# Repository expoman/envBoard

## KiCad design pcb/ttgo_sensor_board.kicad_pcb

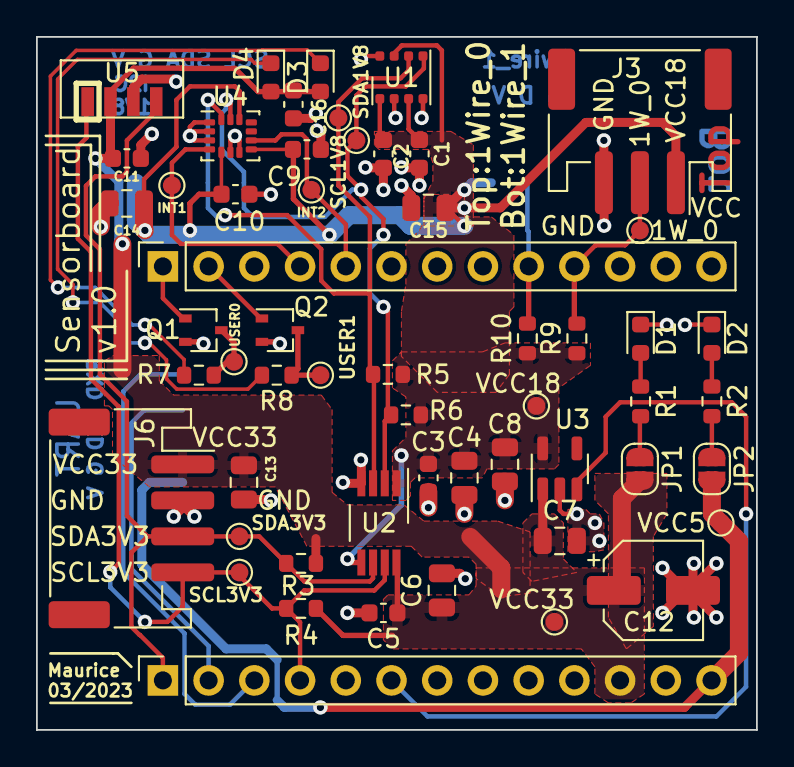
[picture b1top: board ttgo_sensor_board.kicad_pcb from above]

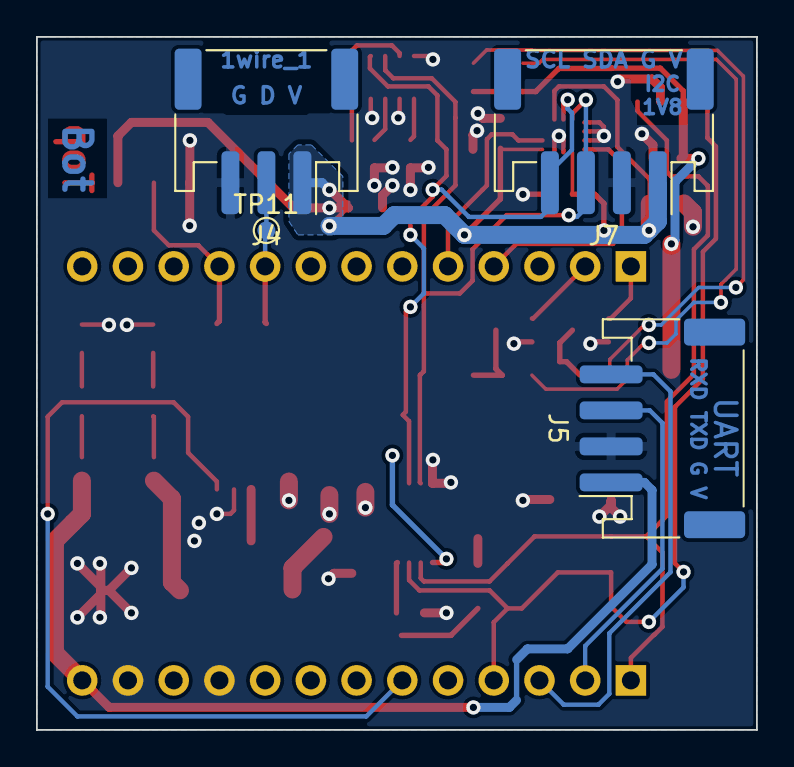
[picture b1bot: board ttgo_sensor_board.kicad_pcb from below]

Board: 2 copper layers, 40.0 x 38.5 mm, 59 parts (4 on the bottom side), 25 nets.

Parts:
C1, C2, C3, C5, C9, C10, C11, C16: 100nF; C_0603_1608Metric
C4, C6, C7, C8, C13, C14, C15: 1uF; C_0805_2012Metric
C12: 10uF; CP_Elec_5x5.3
D1: VCC33_Green; LED_0603_1608Metric
D2: VCC5_Green; LED_0603_1608Metric
D3: U0; LED_0603_1608Metric
D4: U1; LED_0603_1608Metric
J1, J2: Conn_01x13_Female; PinSocket_1x13_P2.54mm_Vertical
J3, J4: Conn_01x03_Female; JST_PH_S3B-PH-SM4-TB_1x03-1MP_P2.00mm_Horizontal
J5, J6, J7: Conn_01x04_Female; JST_PH_S4B-PH-SM4-TB_1x04-1MP_P2.00mm_Horizontal
JP1, JP2: SolderJumper_2_Open; SolderJumper-2_P1.3mm_Open_RoundedPad1.0x1.5mm
Q1, Q2: Q_NMOS_GSD; SOT-323_SC-70
R1: 120; R_0603_1608Metric
R2: 300; R_0603_1608Metric
R3, R4, R5, R6: 10k; R_0603_1608Metric
R7, R8: 82; R_0603_1608Metric
R9, R10: 4k7; R_0603_1608Metric
TP1: VCC33; TestPoint_Pad_D1.0mm
TP2: USER0; TestPoint_Pad_D1.0mm
TP3: USER1; TestPoint_Pad_D1.0mm
TP4: VCC18; TestPoint_Pad_D1.0mm
TP5: VCC5; TestPoint_Pad_D1.0mm
TP6: SCL3V3; TestPoint_Pad_D1.0mm
TP7: SDA3V3; TestPoint_Pad_D1.0mm
TP8: SCL1V8; TestPoint_Pad_D1.0mm
TP9: SDA1V8; TestPoint_Pad_D1.0mm
TP10: 1W_0; TestPoint_Pad_D1.0mm
TP11: 1W_1; TestPoint_Pad_D1.0mm
TP12: INT1; TestPoint_Pad_D1.0mm
TP13: INT2; TestPoint_Pad_D1.0mm
U1: BME680; Bosch_LGA-8_3x3mm_P0.8mm_ClockwisePinNumbering
U2: TCA9800; VSSOP-8_3.0x3.0mm_P0.65mm
U3: TLV70218_SOT23-5; SOT-23-5
U4: LSM6DS3; LGA-14_3x2.5mm_P0.5mm_LayoutBorder3x4y
U5: VEML7700; VEML7700_top_view

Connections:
/1WIRE_DATA0: J2.10, J3.2, R9.2, TP10.1
/1WIRE_DATA1: J2.9, J4.2, R10.2, TP11.1
/EN1V8: J1.6, U3.3 (EN)
/GPIO01: J1.2, J5.3
/GPIO03: J1.3, J5.4
/GPIO21: J1.1, J6.3, R3.2, TP7.1, U2.6 (SDAB), U5.4 (SDA)
/GPIO22: J1.4, J6.4, R4.2, TP6.1, U2.7 (SCLB), U5.1 (SCL)
/GPIO34: J2.4, TP12.1, U4.4 (INT1)
/GPIO35: J2.5, TP13.1, U4.9 (INT2)
/GPIO36: J2.1, Q1.1 (G)
/GPIO39: J2.2, Q2.1 (G)
/SCL1V8: J7.4, R6.2, TP8.1, U1.4 (SCK), U2.2 (SCLA), U4.13 (SCL)
/SDA1V8: J7.3, R5.2, TP9.1, U1.3 (SDI), U2.3 (SDAA), U4.14 (SDA)
/VCC5: J1.13, J5.1, JP2.2 (B), TP5.1
/VCC18: C1.1, C2.1, C3.1, C4.1, C8.1, C9.1, C10.1, C14.1, C15.1, J3.1, J4.1, J7.1, R5.1, R6.1, R9.1, R10.1, TP4.1, U1.2 (CSB), U1.6 (VDDIO), U1.8 (VDD), U2.1 (VCCA), U2.5 (EN), U3.5 (OUT), U4.5 (VDDIO), U4.8 (VDD), U4.12 (CS)
/VCC33: C5.1, C6.1, C7.1, C11.1, C12.1, C13.1, C16.1, D3.2 (A), D4.2 (A), J1.11, J6.1, JP1.2 (B), R3.1, R4.1, TP1.1, U2.8 (VCCB), U3.1 (IN), U5.2 (VDD)
GND: C1.2, C2.2, C3.2, C4.2, C5.2, C6.2, C7.2, C8.2, C9.2, C10.2, C11.2, C12.2, C13.2, C14.2, C15.2, C16.2, D1.1 (K), D2.1 (K), J1.10, J1.12, J3.3, J4.3, J5.2, J6.2, J7.2, Q1.2 (S), Q2.2 (S), U1.1 (GND), U1.5 (SDO), U1.7 (GND), U2.4 (GND), U3.2 (GND), U4.1 (SDO/SA0), U4.2 (SDX), U4.3 (SCX), U4.6 (GND), U4.7 (GND), U5.3 (GND)
unnamed: D1.2 (A), R1.1
unnamed: D2.2 (A), R2.1
unnamed: D3.1 (K), R7.2
unnamed: D4.1 (K), R8.2
unnamed: JP1.1 (A), R1.2
unnamed: JP2.1 (A), R2.2
unnamed: Q1.3 (D), R7.1, TP2.1
unnamed: Q2.3 (D), R8.1, TP3.1

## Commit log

2023-03-24 add gitignore file
2023-03-24 initial commit with kicad files
2023-03-30 remove backupt files
2023-03-30 backup current state
2023-03-30 moved leds and change silkscreen
2023-04-15 production state
2023-06-08 fix schematic after first prototype
2023-06-08 restructure repo: add pcb folder
2023-06-08 add testing versions of firmware
2023-06-29 add basic example for ttgo lora32 v2
2023-06-29 advance ttgo_sensor
    read vcc/vusb voltage and display it on OLED screen
2023-06-29 add sensors
    - add ambient sensor veml7700
    - add bme680 sensor
2023-06-29 fix gpio 26
    gpio 26 was wrongly labeled as gpio 25 in schematic
2023-06-30 restructure code
    move function blocks out of setup and loop routine
2023-06-30 add lsm6ds sensor
2023-06-30 add LoRaLog function
2023-06-30 show more sensor information on display
2023-06-30 add deep sleep of controller
2023-06-30 more refactoring
    add separate sensor_funcs.h/.cpp file
2023-06-30 more refactoring
    add loraFuncs.h/.cpp
2023-07-02 improve log message of gpio pin state
2023-07-02 code cleaning in sensorFuncs.cpp
2023-07-02 fix print of lsm6ds output
    wasn't checked if chip available or not. printed random data always
2023-07-04 fix print of bme680 information
2023-07-04 improve representation of data on oled display
2023-07-10 remove old unused sw states; only working on ttgo_sensor
2023-07-10 fix pin configuration for the ttgo lora32 v1.6 board
2023-07-10 add first draft of example code from ttn_otaa
    sends string to the things network
    has second task for reading sensor data
2023-07-10 add separate timing interval for sensor readings
2023-07-13 move ttn funcs from main file to separate file
    new files ttn_funcs.h/.cpp
2023-07-14 more restructuring of code
    created boards.cpp and moved code from .h in it
    only sensor funcs shows data on display atm
2023-07-14 remove unused define statement
2023-07-14 deactivate sdcard in utilities file
2023-07-14 add second 1wire channel
    changed pin number from first channel from gpio 2 to gpio 13
2023-07-17 started with webserver
    first version shows bme server values
2023-07-21 changes to schematic
2023-07-21 update schematic to kicad 7
2023-07-21 update pcb to kicad7
2023-07-21 update schematic
2023-07-21 add device name to webserver and loralog function
2023-07-21 add own loralog job to scheduler
2023-07-21 register loralog send job in main file
2023-07-21 add main.h and add loralog define
2023-07-26 move ttn_funcs mydata variable
2023-07-26 add webserver control
    text field to change device name
    device name is stored in preference db
2023-07-27 add webserver controls to select logging method
2023-07-27 add function to set lora logging interval via webserver
2023-07-27 add functionality to use logMethod for selecting lora or ttn
2023-07-27 convert return value in string
2023-08-11 get lora data transmission working again
    change scheduler to freertos
    add dataformat definitions
    update lora send function
    send lora data only after readSensor is run once
2023-08-14 small fix when checking onewire sensor
2023-08-14 add reset possibility to webeserver
2023-08-14 update ttn funcs but still disabled
2024-08-07 save work from laptop
    add aliases for compiling and uploading
    add output with lib versions used
